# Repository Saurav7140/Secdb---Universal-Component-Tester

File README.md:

<div align="center">

# SECDB - Universal Component Tester

**An STM32-based diagnostic platform for resistors, capacitors, diodes, and known-pinout BJTs.**

[Description](#description) · [Features](#features) · [Quickstart](#quickstart-guide) · [About](#about)

</div>

## Description

The **Smart Electronic Component Diagnostic Board (SECDB)** is a final-year ECE
project built to identify and evaluate disconnected, unpowered electronic
components. It combines an STM32F401CCU6, a protected shared analog front end,
automatic measurement ranges, calibration channels, and rule-based diagnostic
firmware.

Version 1 targets:

- resistors from **100 ohms to 1 megaohm**;
- capacitors from **100 nF to 100 microfarads**;
- silicon, Schottky, and basic LED diodes;
- known-pinout NPN and PNP BJTs with indicative hFE of approximately **20-500**.

The repository preserves the complete engineering trail: LTspice simulations,
error budgets, firmware sources, KiCad design files, verification reports, and
PCB routing checkpoints.

> [!WARNING]
> The current PCB is an engineering prototype and is **not fabrication-ready**.
> Physical calibration and hardware validation are still required.

## Screenshot and progress

<div align="center">

<strong>Milestone progress</strong><br>

</div>

| Engineering milestone | Status |
|---|:---:|
| Measurement principles and LTspice verification | Complete |
| Range selection and non-ideal error budgets | Complete |
| Shared analog front end and protection design | Complete |
| Firmware architecture and measurement algorithms | Complete at source level |
| KiCad schematic capture and ERC review | Complete |
| PCB placement and critical analog/USB routing | Complete |
| MCU monitor and DUT-drive routing | Complete |
| Remaining display, debug, button, and LED routing | In progress |
| Fabrication and board bring-up | Pending |
| Physical calibration and validation | Pending |

The progress bar is milestone-based; it does not represent manufacturing
readiness. The current board remains at the verified Phase 8D2B checkpoint with
zero KiCad DRC violations and 52 remaining unconnected items. See the
[Phase 8D3 routability review](07_KiCad/PHASE_8D3_ROUTABILITY_REVIEW.md).

## Features

- **Four component modes** - resistor, capacitor, diode, and known-pinout BJT.
- **Automatic resistor ranging** - calibrated 1 kohm, 10 kohm, and 100 kohm
  reference paths.
- **Safe capacitor handling** - discharge verification, guarded charging,
  timeout detection, and a mandatory final-discharge path.
- **Two-polarity diode diagnosis** - orientation, forward conduction, blocking,
  open, short, and ambiguous-result handling.
- **NPN/PNP BJT analysis** - active-region checks, indicative gain calculation,
  and base-off collector-emitter short confirmation.
- **Protected shared AFE** - TMUX switching, OPA391 buffering, ESD protection,
  guarded DUT paths, and calibrated ADC correction.
- **Rule-based diagnostics** - severity, confidence, measured value, reference
  bounds, deviation, and recommended action remain separate.
- **Local interface foundation** - ST7735 display, three-button navigation,
  calibration persistence, and serial diagnostic logging at source level.
- **Reproducible evidence** - simulations, test vectors, ERC/DRC reports,
  manifests, and intentional PCB checkpoints are versioned with the design.

## Prerequisites

Install only the tools needed for the part of the project you want to inspect:

| Tool | Purpose |
|---|---|
| [Git](https://git-scm.com/) | Clone and version the project |
| [KiCad 10](https://www.kicad.org/) | Open the schematic and PCB files |
| [LTspice](https://www.analog.com/ltspice) | Run the simulation decks |
| STM32CubeIDE with STM32F4 HAL | Integrate and target-build the firmware sources |

No dependency installation is required to read the reports or inspect the
existing simulation results.

## Quickstart Guide

### 1. Clone the repository

```bash
git clone https://github.com/Saurav7140/Secdb---Universal-Component-Tester.git
cd Secdb---Universal-Component-Tester
```

### 2. Open the PCB design

Open the following project in KiCad 10:

```text
07_KiCad/SECDB_Component_Tester.kicad_pro
```

The current routed board is `07_KiCad/SECDB_Component_Tester.kicad_pcb`. Review
the latest `PHASE_8*.md` and DRC reports before changing copper.

### 3. Inspect or rerun simulations

Open any `.asc` schematic or `.cir` deck in these folders:

```text
01_LTspice_Verified/
03_Range_Design/
04_Virtual_Breadboard/
05_Shared_Analog_Front_End/
```

Committed `.raw` and `.log` files preserve the verified outputs.

### 4. Explore the firmware

The portable source modules are located at:

```text
06_Firmware/Phase_6_Firmware/Core/Inc/
06_Firmware/Phase_6_Firmware/Core/Src/
```

Create an STM32CubeIDE project for the exact STM32F401CCU6 target, add these
sources, and connect the documented HAL and board callbacks. The firmware has
not yet been target-compiled against a generated CubeIDE project or validated
on physical hardware.

### 5. Follow the engineering record

- [`PROJECT_STATUS_AND_FILE_INDEX.md`](PROJECT_STATUS_AND_FILE_INDEX.md) - broad
  project history and file index.
- [`PHASE_PLAN.md`](PHASE_PLAN.md) - historical roadmap.
- [`07_KiCad/PHASE_8D2B_TWO_LAYER_REFAN_REPORT.md`](07_KiCad/PHASE_8D2B_TWO_LAYER_REFAN_REPORT.md)
  - latest completed PCB-routing checkpoint.
- [`07_KiCad/PHASE_8D3_ROUTABILITY_REVIEW.md`](07_KiCad/PHASE_8D3_ROUTABILITY_REVIEW.md)
  - current PCB decision point.

## About

SECDB is developed by [**Saurav7140**](https://github.com/Saurav7140) as an
electronics and communication engineering final-year project. The goal is to
turn sound measurement principles into a safe, explainable, and reproducible
component-diagnostic platform.

This project is available under the [MIT License](LICENSE). Contributions,
technical reviews, and hardware-validation results are welcome as the design
moves toward fabrication.

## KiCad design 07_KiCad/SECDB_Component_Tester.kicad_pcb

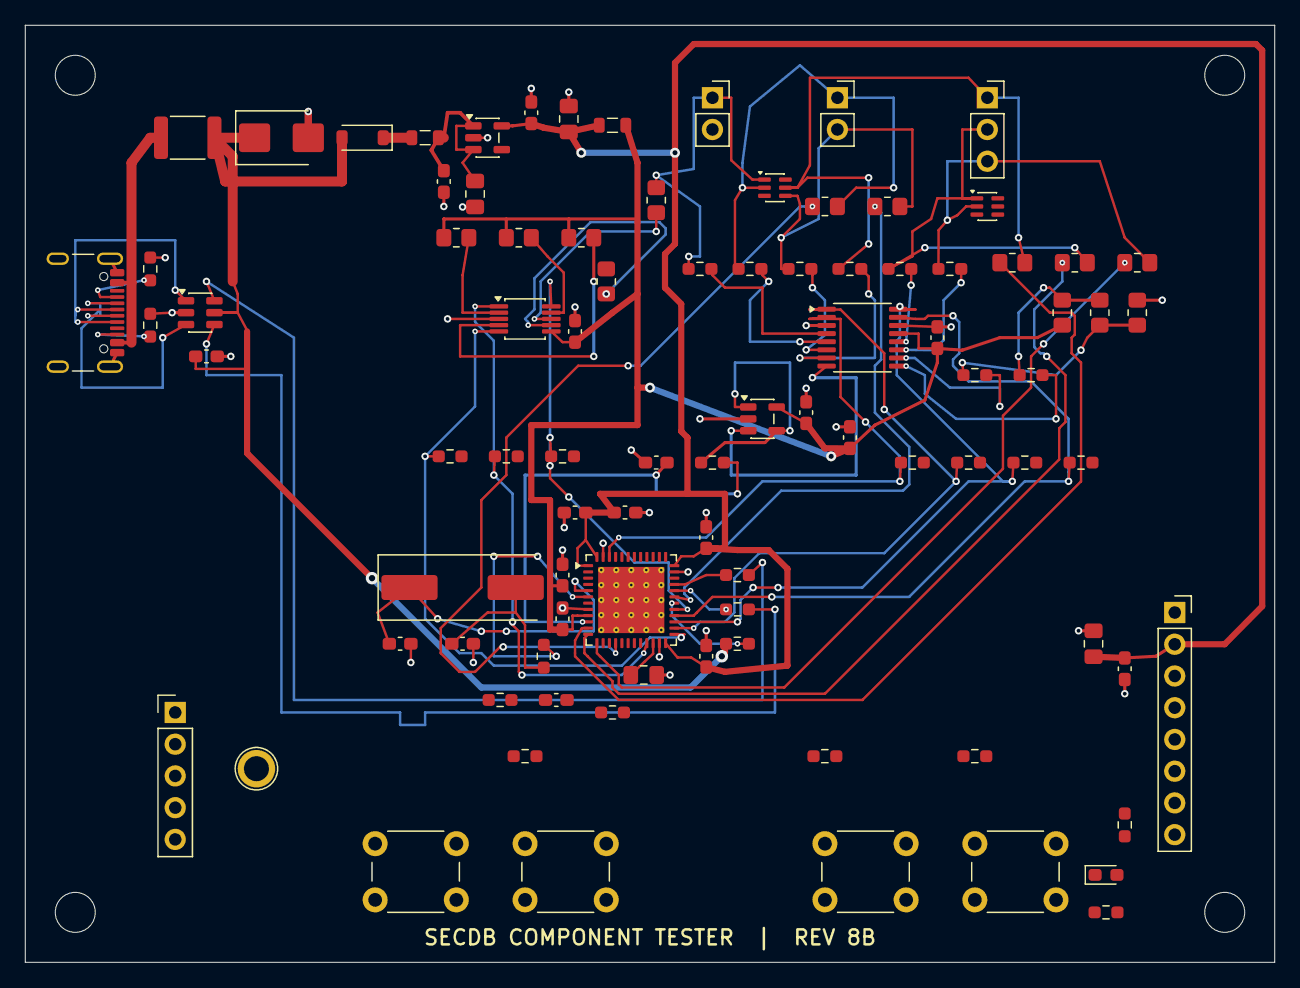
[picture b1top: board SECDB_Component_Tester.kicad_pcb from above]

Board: 2 copper layers, 100.0 x 75.0 mm, 94 parts (0 on the bottom side), 71 nets.

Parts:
C1, C3: 10uF X7R; C_0805_2012Metric_Pad1.18x1.45mm_HandSolder
C2, C4, C5, C6, C7, C8, C9, C11, C15, C17, C18, C19, C22: 100nF X7R; C_0603_1608Metric_Pad1.08x0.95mm_HandSolder
C10, C20: 1uF X7R; C_0603_1608Metric_Pad1.08x0.95mm_HandSolder
C12: 4.7uF X7R low-ESR; C_0805_2012Metric_Pad1.18x1.45mm_HandSolder
C13, C14: 30pF C0G; C_0603_1608Metric_Pad1.08x0.95mm_HandSolder
C16: 1nF C0G 5%; C_0603_1608Metric_Pad1.08x0.95mm_HandSolder
C21: 10uF X5R; C_0805_2012Metric_Pad1.18x1.45mm_HandSolder
D1: SMBJ5.0A-TR; D_SMB
D2: B5819W-7-F; D_SOD-123
ESD1, ESD2: TPD4E1B06DCKR; SOT-363_SC-70-6
F1: MF-MSMF050-2; Fuse_1812_4532Metric
FB1, FB2: BLM21PG221SN1D; L_0805_2012Metric
H1, H2, H3, H4: M3 mounting hole; MountingHole_3.2mm_M3
J1: USB4105-GF-A; USB_C_Receptacle_GCT_USB4105-xx-A_16P_TopMnt_Horizontal
J2: SWD 1x5; PinHeader_1x05_P2.54mm_Vertical
J3: R-C SOCKET; PinSocket_1x02_P2.54mm_Vertical
J4: DIODE A-B; PinSocket_1x02_P2.54mm_Vertical
J5: BJT E-B-C; PinSocket_1x03_P2.54mm_Vertical
J6: ST7735 1x8 BOARD HEADER; PinSocket_1x08_P2.54mm_Vertical
LED1: STATUS GREEN; LED_0603_1608Metric_Pad1.05x0.95mm_HandSolder
R1, R2: 5.1k 1%; R_0603_1608Metric_Pad0.98x0.95mm_HandSolder
R3, R12, R25, R26, R27, R28, R29, R30, R31, R32: 1k 1%; R_0603_1608Metric_Pad0.98x0.95mm_HandSolder
R4, R5: 22R 1%; R_0603_1608Metric_Pad0.98x0.95mm_HandSolder
R6, R42: 0R FIT; R_0603_1608Metric_Pad0.98x0.95mm_HandSolder
R7, R8, R9, R10, R11: 10k 1%; R_0603_1608Metric_Pad0.98x0.95mm_HandSolder
R13, R14, R15, R16, R17, R18, R19: 100k 1%; R_0603_1608Metric_Pad0.98x0.95mm_HandSolder
R20, R23: 1k 0.1% 25ppm; R_0805_2012Metric_Pad1.20x1.40mm_HandSolder
R21, R33, R34, R35: 10k 0.1% 25ppm; R_0805_2012Metric_Pad1.20x1.40mm_HandSolder
R22: 100k 0.1% 25ppm; R_0805_2012Metric_Pad1.20x1.40mm_HandSolder
R24: 330R 0.1%; R_0805_2012Metric_Pad1.20x1.40mm_HandSolder
R36, R37, R40: 1k 0.1%; R_0805_2012Metric_Pad1.20x1.40mm_HandSolder
R38: 100R 1%; R_0805_2012Metric_Pad1.20x1.40mm_HandSolder
R39: 1M 0.1%; R_0805_2012Metric_Pad1.20x1.40mm_HandSolder
R41: 100R 1%; R_0603_1608Metric_Pad0.98x0.95mm_HandSolder
SW1: RESET; SW_PUSH_6mm
SW2: MODE; SW_PUSH_6mm
SW3: UP; SW_PUSH_6mm
SW4: DOWN; SW_PUSH_6mm
TP1: BOOT0 SERVICE; TestPoint_Plated_Hole_D2.0mm
U1: STM32F401CCU6; QFN-48-1EP_7x7mm_P0.5mm_EP5.3x5.3mm_ThermalVias
U2: TMUX1104DGSR; MSOP-10_3x3mm_P0.5mm
U3: TMUX1108PWR; TSSOP-16_4.4x5mm_P0.65mm
U4: OPA391DBVR; SOT-23-5
U5: AP2112K-3.3TRG1; SOT-23-5
U6: USBLC6-2SC6; SOT-23-6
Y1: ABLS-8.000MHZ-B2-T; Crystal_SMD_HC49-SD

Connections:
3V3_A: C10.1, C11.1, C17.1, C18.1, C19.1, C20.1, FB2.2, R20.1, R21.1, R22.1, R33.1, U1.9, U2.6, U3.13, U4.5
3V3_D: C3.1, C4.1, C6.1, C7.1, C8.1, C9.1, C21.1, C22.1, FB2.1, J2.1, J6.2, R7.1, R9.1, R10.1, R11.1, R42.1, U1.1, U1.24, U1.36, U1.48, U5.5
5V_DIODE: D2.1, FB1.1
ADC_BUFFERED: C16.1, R41.2, U1.10
BJT_B: ESD2.1, J5.2, R29.1, R39.2
BJT_B_GPIO: R39.1, U1.12
BJT_C: ESD2.2, J5.3, R30.1, R40.2
BJT_C_GPIO: R40.1, U1.13
BJT_E: ESD1.5, J5.1, R28.1, R38.2
BJT_E_GPIO: R38.1, U1.11
BOOT0: R8.1, TP1.1, U1.45
BTN_DOWN: R11.2, SW4.1, U1.4
BTN_MODE: R9.2, SW2.1, U1.2
BTN_UP: R10.2, SW3.1, U1.3
CAL_1V1: R31.1, R34.2, R35.1
CAL_2V2: R32.1, R33.2, R34.1
DIODE_A: ESD1.2, J4.1, R26.1, R36.2
DIODE_A_GPIO: R36.1, U1.16
DIODE_B: ESD1.4, J4.2, R27.1, R37.2
DIODE_B_GPIO: R37.1, U1.31
GND: C1.2, C2.2, C3.2, C4.2, C5.2, C6.2, C7.2, C8.2, C9.2, C10.2, C11.2, C12.2, C13.2, C14.2, C15.2, C16.2, C17.2, C18.2, C19.2, C20.2, C21.2, C22.2, D1.2, ESD1.3, ESD2.3, J1.A1, J1.A12, J1.B1, J1.B12, J1.SH, J2.3, J3.2, J6.1, LED1.1, R1.2, R2.2, R8.2, R13.2, R14.2, R15.2, R16.2, R17.2, R18.2, R19.2, R23.2, R35.2, SW1.2, SW2.2, SW3.2, SW4.2, U1.8, U1.23, U1.35, U1.47, U1.49, U2.3, U3.3, U3.14, U4.2, U5.2, U6.2
HSE_IN: C13.1, U1.5, Y1.1
HSE_OUT: R6.2, U1.6
HSE_XTAL_OUT: C14.1, R6.1, Y1.2
LDO_IN: C1.1, C2.1, FB1.2, U5.1, U5.3
LED_ANODE: LED1.2, R12.2
NRST: C15.1, J2.5, R7.2, SW1.1, U1.7
OPA_OUT: R41.1, U4.1, U4.4
RC_INTERNAL: R24.1, U2.8
RC_SOCKET: ESD1.1, J3.1, R24.2, R25.1
SENSE_COM: U3.8, U4.3
SNS_A0: R17.1, U1.26, U3.1
SNS_A1: R18.1, U1.27, U3.16
SNS_A2: R19.1, U1.28, U3.15
SNS_BJT_B: R29.2, U3.12
SNS_BJT_C: R30.2, U3.11
SNS_BJT_E: R28.2, U3.7
SNS_CAL_1V1: R31.2, U3.10
SNS_CAL_2V2: R32.2, U3.9
SNS_DIODE_A: R26.2, U3.5
SNS_DIODE_B: R27.2, U3.6
SNS_EN: R16.1, U1.46, U3.2
SNS_RC: R25.2, U3.4
SRC_1K: R20.2, U2.2
SRC_10K: R21.2, U2.9
SRC_100K: R22.2, U2.4
SRC_A0: R14.1, U1.21, U2.1
SRC_A1: R15.1, U1.29, U2.10
SRC_DISCHARGE: R23.1, U2.7
SRC_EN: R13.1, U1.25, U2.5
STATUS_LED: R12.1, U1.44
SWCLK: J2.4, U1.37
SWDIO: J2.2, U1.34
TFT_BL: J6.8, R42.2
TFT_CS: J6.5, U1.14
TFT_DC: J6.6, U1.19
TFT_MOSI: J6.4, U1.17
TFT_RST: J6.7, U1.18
TFT_SCK: J6.3, U1.15
USB_CC1: J1.A5, R1.1
USB_CC2: J1.B5, R2.1
USB_DM_CONN: J1.A7, J1.B7, U6.3
USB_DM_ESD: R5.1, U6.4
USB_DM_MCU: R5.2, U1.32
USB_DP_CONN: J1.A6, J1.B6, U6.1
USB_DP_ESD: R4.1, U6.6
USB_DP_MCU: R4.2, U1.33
USB_VBUS_FUSED: C5.1, D1.1, D2.2, F1.2, R3.1, U6.5
USB_VBUS_RAW: F1.1, J1.A4, J1.A9, J1.B4, J1.B9
USB_VBUS_SENSE: R3.2, U1.30
VCAP_1: C12.1, U1.22

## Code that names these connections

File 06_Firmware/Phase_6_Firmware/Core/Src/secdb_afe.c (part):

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#define SECDB_ANALOG_SETTLE_US      200UL

typedef enum {
    SRC_1K = 0,
    SRC_10K = 1,
    SRC_100K = 2,
    SRC_DISCHARGE = 3
} source_channel_t;

typedef enum {
    SNS_RC = 0,
    SNS_DIODE_A = 1,
    SNS_DIODE_B = 2,
    SNS_BJT_E = 3,
    SNS_BJT_B = 4,
    SNS_BJT_C = 5,
    SNS_CAL_1V1 = 6,
    SNS_CAL_2V2 = 7
} sense_channel_t;

static secdb_afe_mode_t current_mode = SECDB_AFE_DISABLED;
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

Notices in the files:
README.md:
License: MIT
